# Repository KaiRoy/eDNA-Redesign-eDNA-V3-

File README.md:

# eDNA Board V3.0 - A Redesign of the OPEnS Lab's eDNA Control Board
A redesign of the Main Control Board for the eDNA Sampler

## Table of Contents

- [Description](#description)
- [Design](#design)
- [Current State](#current-state-of-the-project)
- [Post Project Notes](#post-project-notes)
- [Installation](#installation) <!-- Should I have Installation and Usage above or below the Design, Current State, Changes, etc? -->
- [Usage](#usage)
- [Credits](#credits)
- [License](#license)

## Description

I have worked on the eDNA project at the OPEnS Lab for the past two years and during that time I noticed a couple of things that I wanted to change about the current electronics board (Dubbed eDNA Electronics V2). Because of other responsiblities, I never had the time to make those changes so I decided to make a Project Course out of it to ensure that I would have the time. This meant I had to limit the number of changes that I wanted to make for time purposes. Here were the goals for the project/redesign:
- Allowing for 5V sensor support (mainly I2C sensor support)
- Redesigning the Power Management Circuits to allow for easier integration of wake-from-sleep interrupts
- Write Documentation for this version and the previous version, since no documentation does not exist

## Designs

Most of the circuits on this board have already been designed and I had no intention of fundamentally changing them in this redesign. The circuits that are being redesigned are the sleep/power management circuit and the logic level converter circuit. The other circuits only get changed on the PCB Layout level, changing as many two-terminal components from 1206 to 0805 and general rearrangement of the PCB Layout.

The power management (PM) system was designed to disable the output of the voltage regulator (Vreg). This would conserve a lot of power as most of the circuits and devices would be powered off, with only the RTC and parts of the PM circuit still functioning. This circuit work by using a D Flip Flop connected to the Microcontroller and the RTC to enable or disable the output of the Vreg Circuit. Because of this design, the microcontroller was completely off with only the RTC Interrupt able to wake up the microcontroller. This makes it difficult to add additional external interrupts to wake the system from sleep. We encountered this problem when we tried to add a button that would wake the system from sleep and trigger an operation.

Another project from the OPEnS Lab created a PM circuit that is used by the majority of projects at the OPEnS Lab, the eDNA project being one of the few projects that do not. This project, called the Hypnos Board, uses a series of MOSFETs to enable and disable power lines going to peripheral devices, leaving the microcontroller powered. We can further conserve power by putting the microctronller into a deep sleep. This will allow us to easily add new wake-from-sleep interrupts while still conserving power.

According to other employees at the OPEnS Lab and some online research the Adafruit Feather M0, the OPEnS Lab's Microcontroller of choice, consumes 1-2mA of current while in a software sleep. Based on the size of the battery, power consumption during operation, and the size of the battery, the approximate current draw while in sleep should be little enough that the sampler can complete a full 24 operations over the course of 30 days, which is what the eDNA Sampler was designed to be able to do. 

The change in the logic level converter circuit was needed because 5V I2C sensor support was desired for the eDNA Sampler. This is because many I2C sensors function off of 5V and limiting the system to only 3.3V I2C sensors can make it difficult to add desired features or functionality. The current logic level converter, a module from Sparkfun, only has 4-channels of conversion with three already in use. Since the circuit needed to be changed anyway, instead of using a module like the one from SparkFun, an IC was found to serve the purpose. The IC used in the v3.0 is the TXS0108E, an eight channel logic level converter.

## Current State of the Project

I was able to do some testing by the end of the term and discovered a couple of mistakes. These mistakes had to do with how I wired certain components up on at the schematic level. I misconnceted the Sleep LED and the RTC_INT Pull-Up Resistor. The sleep LED is less important but rewiring it to my always-on 3.3V line instead of my peripheral device 3.3V line allowed me to better see if the sleep switch/circuit was functioning correctly. The RTC_INT Pull-Up Resistor on the other had was a major error. I had connected the resistor to the Peripheral 3.3V line instead of the always-on 3.3V, meaning that the power would be cut during sleep. Since the RTC_INT is necessary for waking up, this caused a constant cycle of the sleep mode being enabled, the drop in voltage triggering the interrupt, the system waking up, realizing that it has not reached the desired wake-up time, and falling back asleep. 

These mistakes could have been caught if I spent more time at the planning and schematic levels review the design before moving onto the PCB design. Something I plan to allocate time for in future projects. Because of this wiring issues, this version of the board remains untested. There are plans to cut the necessary traces and solder splice wires to reconenct the components and continue testing.

## Post Project Notes

In the future I would spend a lot more time verifying the schematic level of my design to ensure that I have no obvious mistakes, such as the wiring mistakes that I made in the first version of this board. If I am working on a project that is time limited, I would be sure to allocate more than enough time to spend verifying my design/schematic before moving onto the development of the PCB. 

I would also use KiCad over EAGLE in the future if possible. Having used both of the EDA softwares, I have developed a preference towards KiCad over EAGLE due to KiCad's Hotkey and Shortcut based control scheme. This has made my workflows in KiCad feel much smoother to me than my workflows in EAGLE have. In addition, I have been using the free version of EAGLE which has limitations on what can be done in the software, while KiCad does not. 

Below are a list of changes that I would recommend be made in future version of this board. I have split it into two categories as there is a difference between the changes that I would personally like to make, and the changes that I would recommend to the OPEnS Lab. Since the OPEnS Lab cannot simply make changes for the sack of making changes, the changes I recommend are ones that I see having a better Benefit-Cost Ratio conisdering the current state of the Project. 

What I would recommend for the next OPEnS Lab Version:
- Find a new Voltage Regulator IC/Redesign the Vreg Circuit
	- This IC was chosen as it had an Enable pin and its was automotive grade. Since neither of these specifications are that important I would recommend looking into a new IC that is easier to come by, since this one has been very hard to purchase in the past. 
- Redesign the Shift Registers to use the existing SPI Pins on the Feather M0
	- If that is not possible with the current Shift Registers for any reason, I would recommend finiding new Shift Registers to use in the design.

For my own personal version (outside of the OPEnS Lab):
- Switch to an ESP32 based design
	- Deep Sleep Functionality
  	- Built in RTC and WiFi Modules
  	- Similar amount of I/O Pins
	- Larger Program Memory (Our debug code is limited by the size of the Feather M0 Program Memory)
- Redesign the PCB with the intention of purchasing them preassembled. 
	- This would allow for smaller componenets to be used, components too small to be easily assembled by hand. 
	- This would allow for a two-sided PCB design i.e components on either side of the PCB, something that is hard to do by hand.

## Installation

What EDA libraries and files are needed for this project?
- eDNA Library
- Various Component Libraries
<!-- Make a singular Library for all of the components Symbols and footprints -->
<!-- Insert a link to a library guide or make my own -->

<!-- Add a link to the firmware installation guide -->
<!-- Note which code version to use -->

<!--
## Usage

Provide instructions and examples for use. Include screenshots as needed.

To add a screenshot, create an `assets/images` folder in your repository and upload your screenshot to it. Then, using the relative filepath, add it to your README using the following syntax:

    ```md
    
    ```

## Features

If your project has a lot of features, list them here.

## Tests

-->

## Credits

List your collaborators, if any, with links to their GitHub profiles.
- Nathan Jesudason: Modifying the [Sampler Code](https://github.com/OPEnSLab-OSU/ednaServer/tree/54-revamp-sleep-system) Changes for testing

If you used any third-party assets that require attribution, list the creators with links to their primary web presence in this section.
- OPEnS Lab's [Hypnos Board V3.4](https://github.com/OPEnSLab-OSU/OPEnS-Hypnos)
- A branch of the [ednaServer](https://github.com/OPEnSLab-OSU/ednaServer/tree/54-revamp-sleep-system) code
<!-- Link the Symbols and Footprints used? -->

## License

Licensed under the [CERN-OHL-S-2.0](LICENSE.txt) License

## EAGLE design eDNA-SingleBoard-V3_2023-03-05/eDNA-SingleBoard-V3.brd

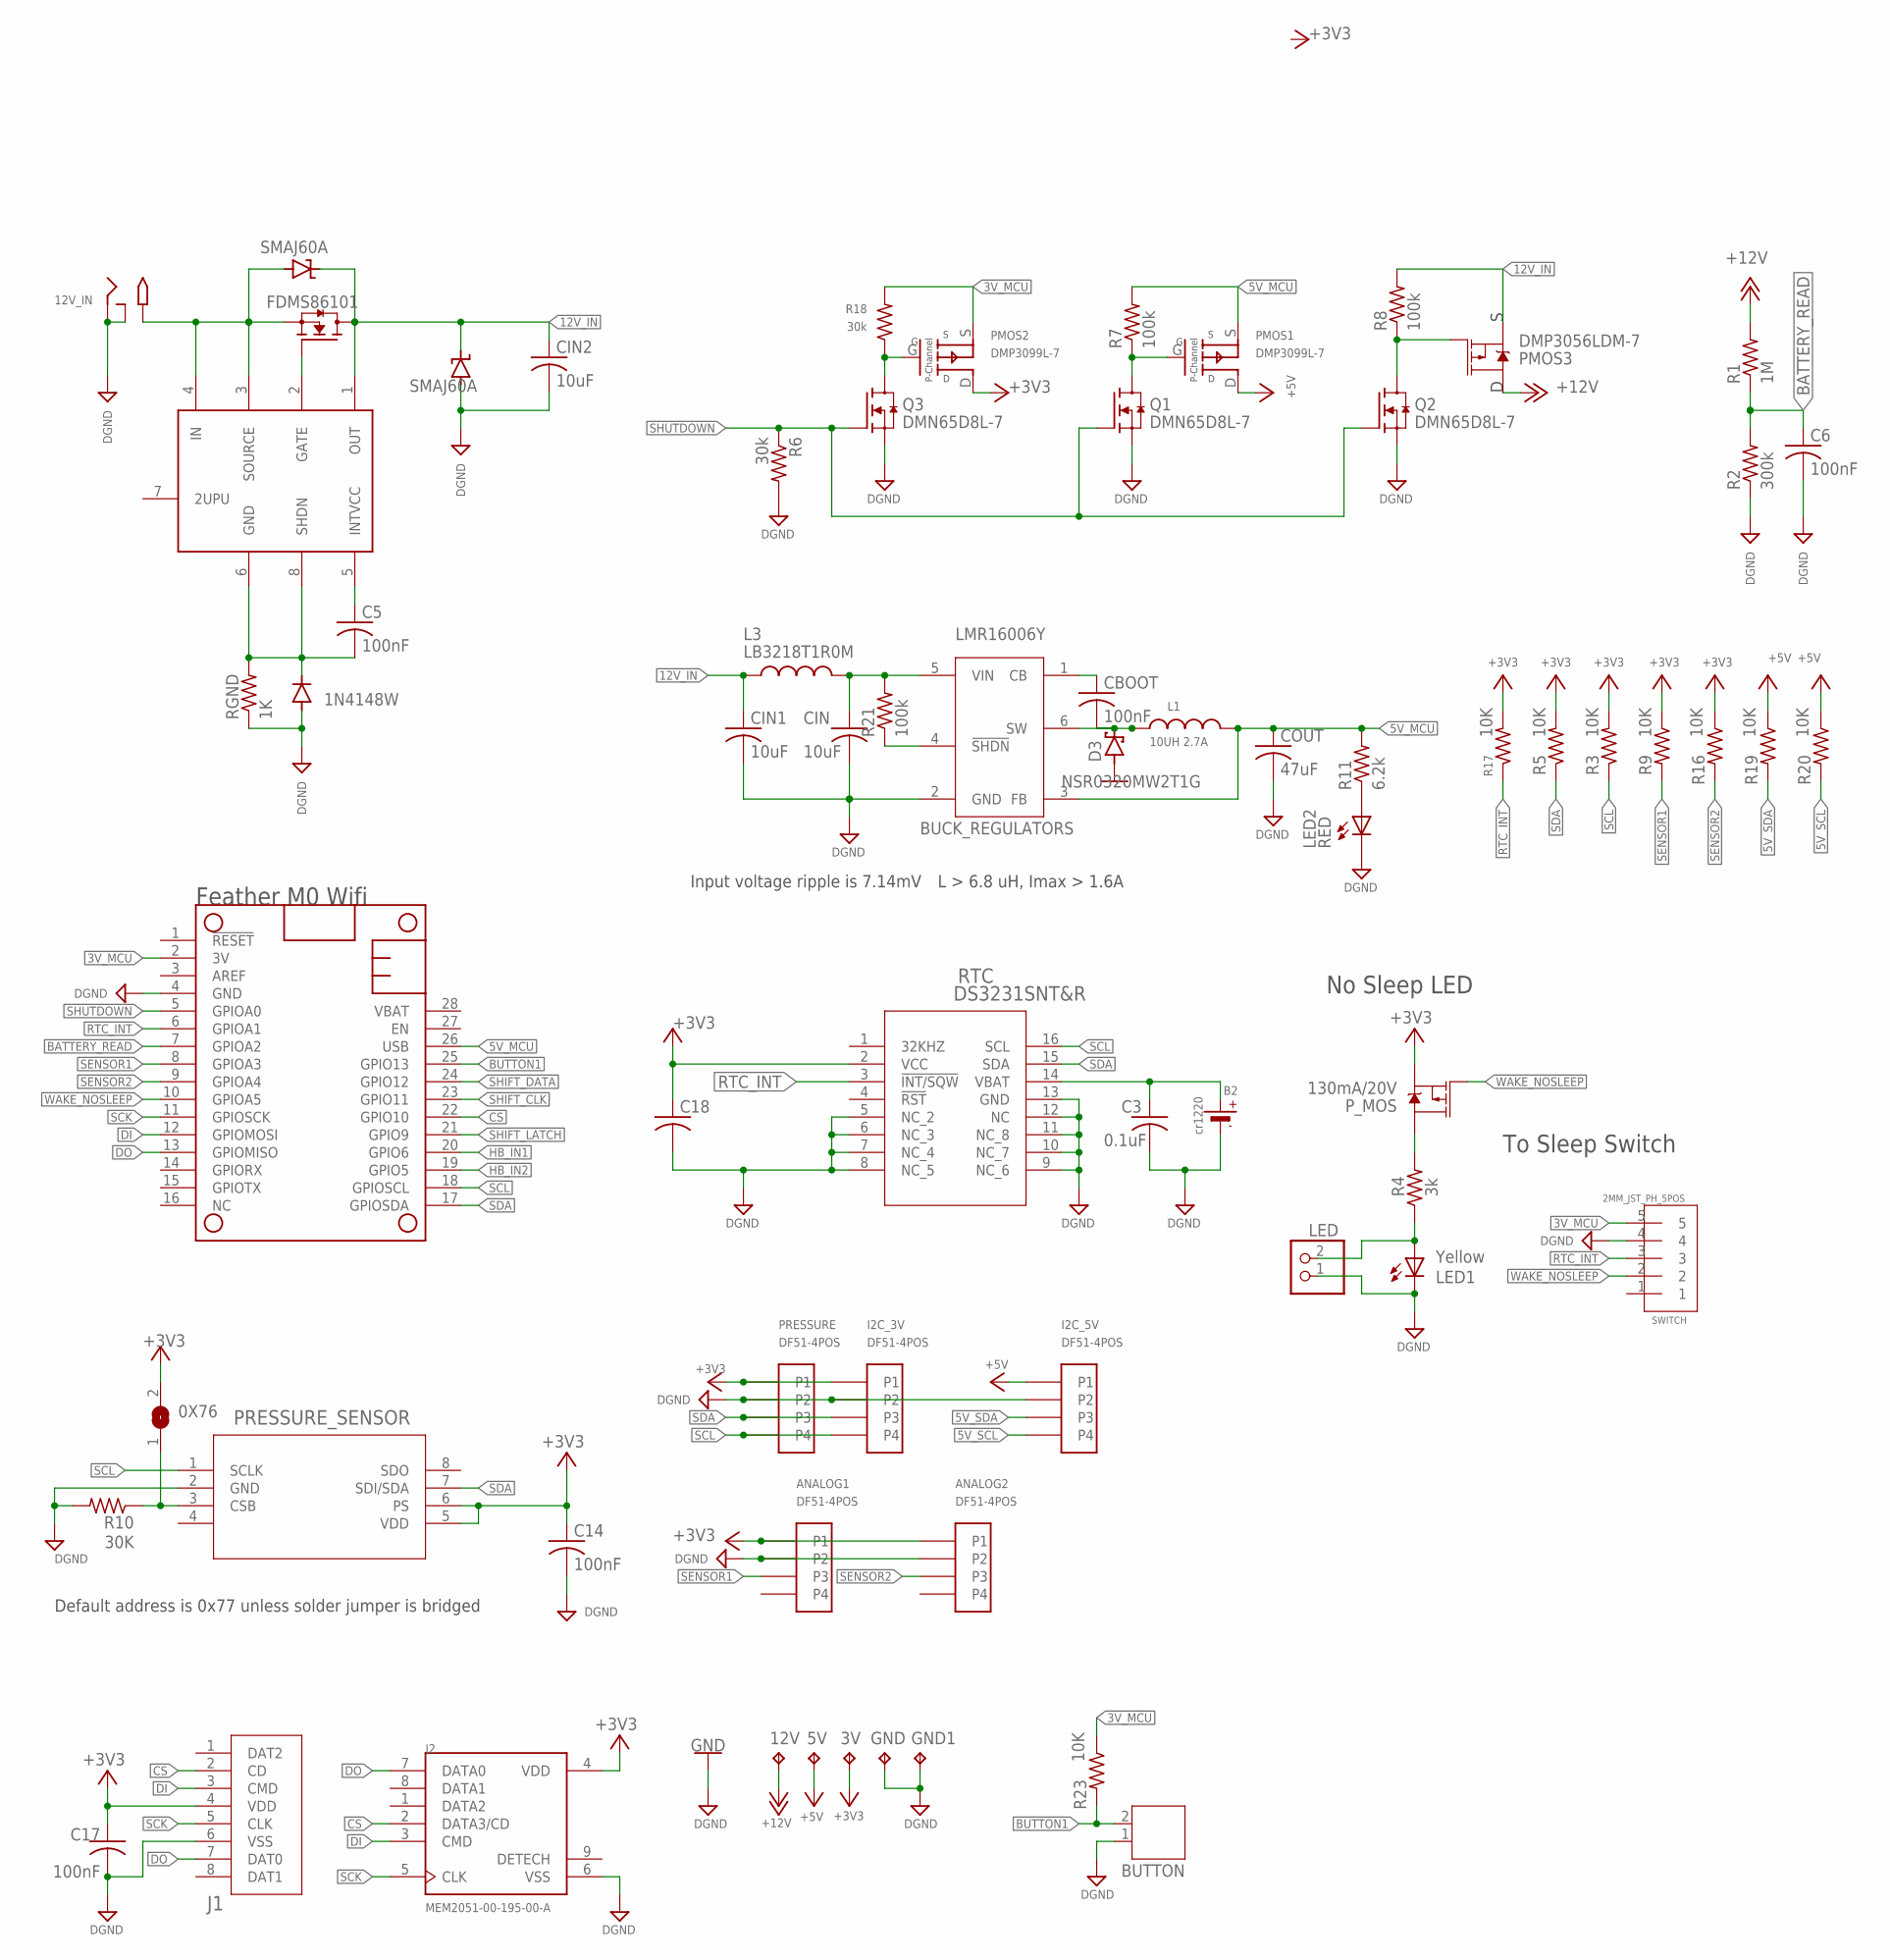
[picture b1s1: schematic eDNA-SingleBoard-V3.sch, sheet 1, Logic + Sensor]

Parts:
0X76: SJ
3V, 5V, 12V: TPPAD1-13; P1-13
12V_IN: 2.1MMJACKSMT; DCJACK_2MM_SMT
ANALOG1, ANALOG2: DF51-4POS
B2: cr1220; CR1220-2
BUTTON: JST-PH2
C3: 0.1uF; C0805
C5, C6, C14, C17, C18: 100nF; C0805
CBOOT: 100nF; C0805
CIN, CIN1, CIN2: 10uF; C0805
COUT: 47uF; C0805
D2: 1N4148W; SOD-123_MINI-SMA
D3: NSR0320MW2T1G; SOD323_ST
D4, D5: SMAJ60A; DO_214
GND, GND1: TPPAD1-13; P1-13
I2C_3V, I2C_5V: DF51-4POS
J1: PJS008U-3000-0; CONN_PJS008U-3000-0_YAM
J2: MEM2051-00-195-00-A; GCT_MEM2051-00-195-00-A
L1: 10UH 2.7A; WE-MAPI_40XX
L3: LB3218T1R0M; INDC3218X200N
LED: 2.5MM_JST_UP_2POS; JST_2POS_2.5MM_UP
LED1: Yellow; CHIPLED_0805
LED2: RED; CHIPLED_0805
MS1: FEATHERWING
NMOS: FDMS86101; 8-POWERTDFN
PMOS1, PMOS2: DMP3099L-7; SOT-23-3
PMOS3: DMP3056LDM-7; SOT23-6
PRESSURE: DF51-4POS
PRESSURE_SENSOR: MS580302BA01-00; MS5803-02BA01
P_MOS: 130mA/20V; SOT23-3
Q1, Q2, Q3: DMN65D8L-7; SOT23-S
R1: 1M; R0805
R2: 300k; R0805
R3, R5, R9, R16, R17, R19, R20, R23: 10K; R0805
R4: 3k; R0805
R6, R18: 30k; RES_1206
R7, R8, R21: 100k; RES_1206
R10: 30K; R0805
R11: 6.2k; R0805
RGND: 1K; R0805
RTC: DS3231SNT&R; 21-0042B_16
SWITCH: 2MM_JST_PH_5POS; 2MM_5POS_HEADER
U$7: LTC4372; SOP65P640X120-8N
VREG: BUCK_REGULATORS; SOT23-6@1

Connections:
3V_MCU: MS1.2 (3V), PMOS2.S, R18.2, R23.1, SWITCH.5
5V_MCU: COUT.1, L1.2, MS1.26 (USB), PMOS1.S, R7.2, R11.2, VREG.3 (FB)
5V_SCL: I2C_5V.P$4 (P4), R20.2; also elsewhere on the board
5V_SDA: I2C_5V.P$3 (P3), R19.2; also elsewhere on the board
12V_IN: CIN1.1, CIN2.1, D4.C, D5.C, L3.1, NMOS.5 (D), NMOS.6 (D), NMOS.7 (D), NMOS.8 (D), NMOS.9 (D), PMOS3.4 (S), R8.2, U$7.1 (OUT)
+3V3: 0X76.2, 3V.TP, ANALOG1.P$1 (P1), ANALOG2.P$1 (P1), C14.1, C17.1, C18.1, I2C_3V.P$1 (P1), J1.4 (VDD), J2.4 (VDD), PMOS2.D, PRESSURE.P$1 (P1), PRESSURE_SENSOR.5 (VDD), PRESSURE_SENSOR.6 (PS), P_MOS.2 (S), R3.2, R5.2, R9.1, R16.1, R17.2, RTC.2 (VCC); also elsewhere on the board
+5V: 5V.TP, I2C_5V.P$1 (P1), PMOS1.D, R19.1, R20.1; also elsewhere on the board
+12V: 12V.TP, PMOS3.1 (D), PMOS3.2 (D), PMOS3.5 (D), PMOS3.6 (D), R1.2; also elsewhere on the board
+12V_NON_PROTECT: 12V_IN.PWR2 (TIP), D5.A, NMOS.1 (S), NMOS.2 (S), NMOS.3 (S), U$7.3 (SOURCE), U$7.4 (IN)
BATTERY_READ: C6.1, MS1.7 (GPIOA2), R1.1, R2.2
BUTTON1: BUTTON.2, MS1.25 (GPIO13), R23.2
CS: J1.2 (CD), J2.2 (DATA3/CD), MS1.22 (GPIO10)
DGND: 12V_IN.GND (RING), 12V_IN.GNDBREAK (RING_SW), ANALOG1.P$2 (P2), ANALOG2.P$2 (P2), B2.-, BUTTON.1, C3.2, C6.2, C14.2, C17.2, C18.2, CIN.2, CIN1.2, CIN2.2, COUT.2, D2.A, D4.A, GND.TP, GND1.TP, I2C_3V.P$2 (P2), I2C_5V.P$2 (P2), J1.6 (VSS), J2.6 (VSS), LED.1, LED1.C, LED2.C, MS1.4 (GND), PRESSURE.P$2 (P2), PRESSURE_SENSOR.2 (GND), Q1.2 (S), Q2.2 (S), Q3.2 (S), R2.1, R6.2, R10.2, RGND.1, RTC.5 (NC_2), RTC.6 (NC_3), RTC.7 (NC_4), RTC.8 (NC_5), RTC.9 (NC_6), RTC.10 (NC_7), RTC.11 (NC_8), RTC.12 (NC), RTC.13 (GND), SWITCH.4, VREG.2 (GND); also elsewhere on the board
DI: J1.3 (CMD), J2.3 (CMD), MS1.12 (GPIOMOSI)
DO: J1.7 (DAT0), J2.7 (DATA0), MS1.13 (GPIOMISO)
GND: D3.A
HB_IN1: MS1.20 (GPIO6); also elsewhere on the board
HB_IN2: MS1.19 (GPIO5); also elsewhere on the board
unnamed: B2.+, C3.1, RTC.14 (VBAT)
unnamed: P_MOS.3 (D), R4.2
unnamed: PMOS3.3 (G), Q2.3 (D), R8.1
unnamed: 0X76.1, PRESSURE_SENSOR.3 (CSB), R10.1
unnamed: NMOS.4 (G), U$7.2 (GATE)
unnamed: LED.2, LED1.A, R4.1
unnamed: PMOS1.G, Q1.3 (D), R7.1
unnamed: LED2.A, R11.1
unnamed: R21.1, VREG.4 (!SHDN)
unnamed: PMOS2.G, Q3.3 (D), R18.1
unnamed: CIN.1, L3.2, R21.2, VREG.5 (VIN)
unnamed: CBOOT.1, VREG.1 (CB)
unnamed: CBOOT.2, D3.C, L1.1, VREG.6 (SW)
unnamed: C5.1, U$7.5 (INTVCC)
unnamed: C5.2, D2.C, RGND.2, U$7.6 (GND), U$7.8 (SHDN)
RTC_INT: MS1.6 (GPIOA1), R17.1, RTC.3 (!INT/SQW), SWITCH.3
SCK: J1.5 (CLK), J2.5 (CLK), MS1.11 (GPIOSCK)
SCL: I2C_3V.P$4 (P4), MS1.18 (GPIOSCL), PRESSURE.P$4 (P4), PRESSURE_SENSOR.1 (SCLK), R3.1, RTC.16 (SCL); also elsewhere on the board
SDA: I2C_3V.P$3 (P3), MS1.17 (GPIOSDA), PRESSURE.P$3 (P3), PRESSURE_SENSOR.7 (SDI/SDA), R5.1, RTC.15 (SDA); also elsewhere on the board
SENSOR1: ANALOG1.P$3 (P3), MS1.8 (GPIOA3), R9.2
SENSOR2: ANALOG2.P$3 (P3), MS1.9 (GPIOA4), R16.2
SHIFT_CLK: MS1.23 (GPIO11); also elsewhere on the board
SHIFT_DATA: MS1.24 (GPIO12); also elsewhere on the board
SHIFT_LATCH: MS1.21 (GPIO9); also elsewhere on the board
SHUTDOWN: MS1.5 (GPIOA0), Q1.1 (G), Q2.1 (G), Q3.1 (G), R6.1
WAKE_NOSLEEP: MS1.10 (GPIOA5), P_MOS.1 (G), SWITCH.2

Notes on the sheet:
No Sleep LED
Feather M0 Wifi
To Sleep Switch
Input voltage ripple is 7.14mV
L > 6.8 uH, Imax > 1.6A
Default address is 0x77 unless solder jumper is bridged

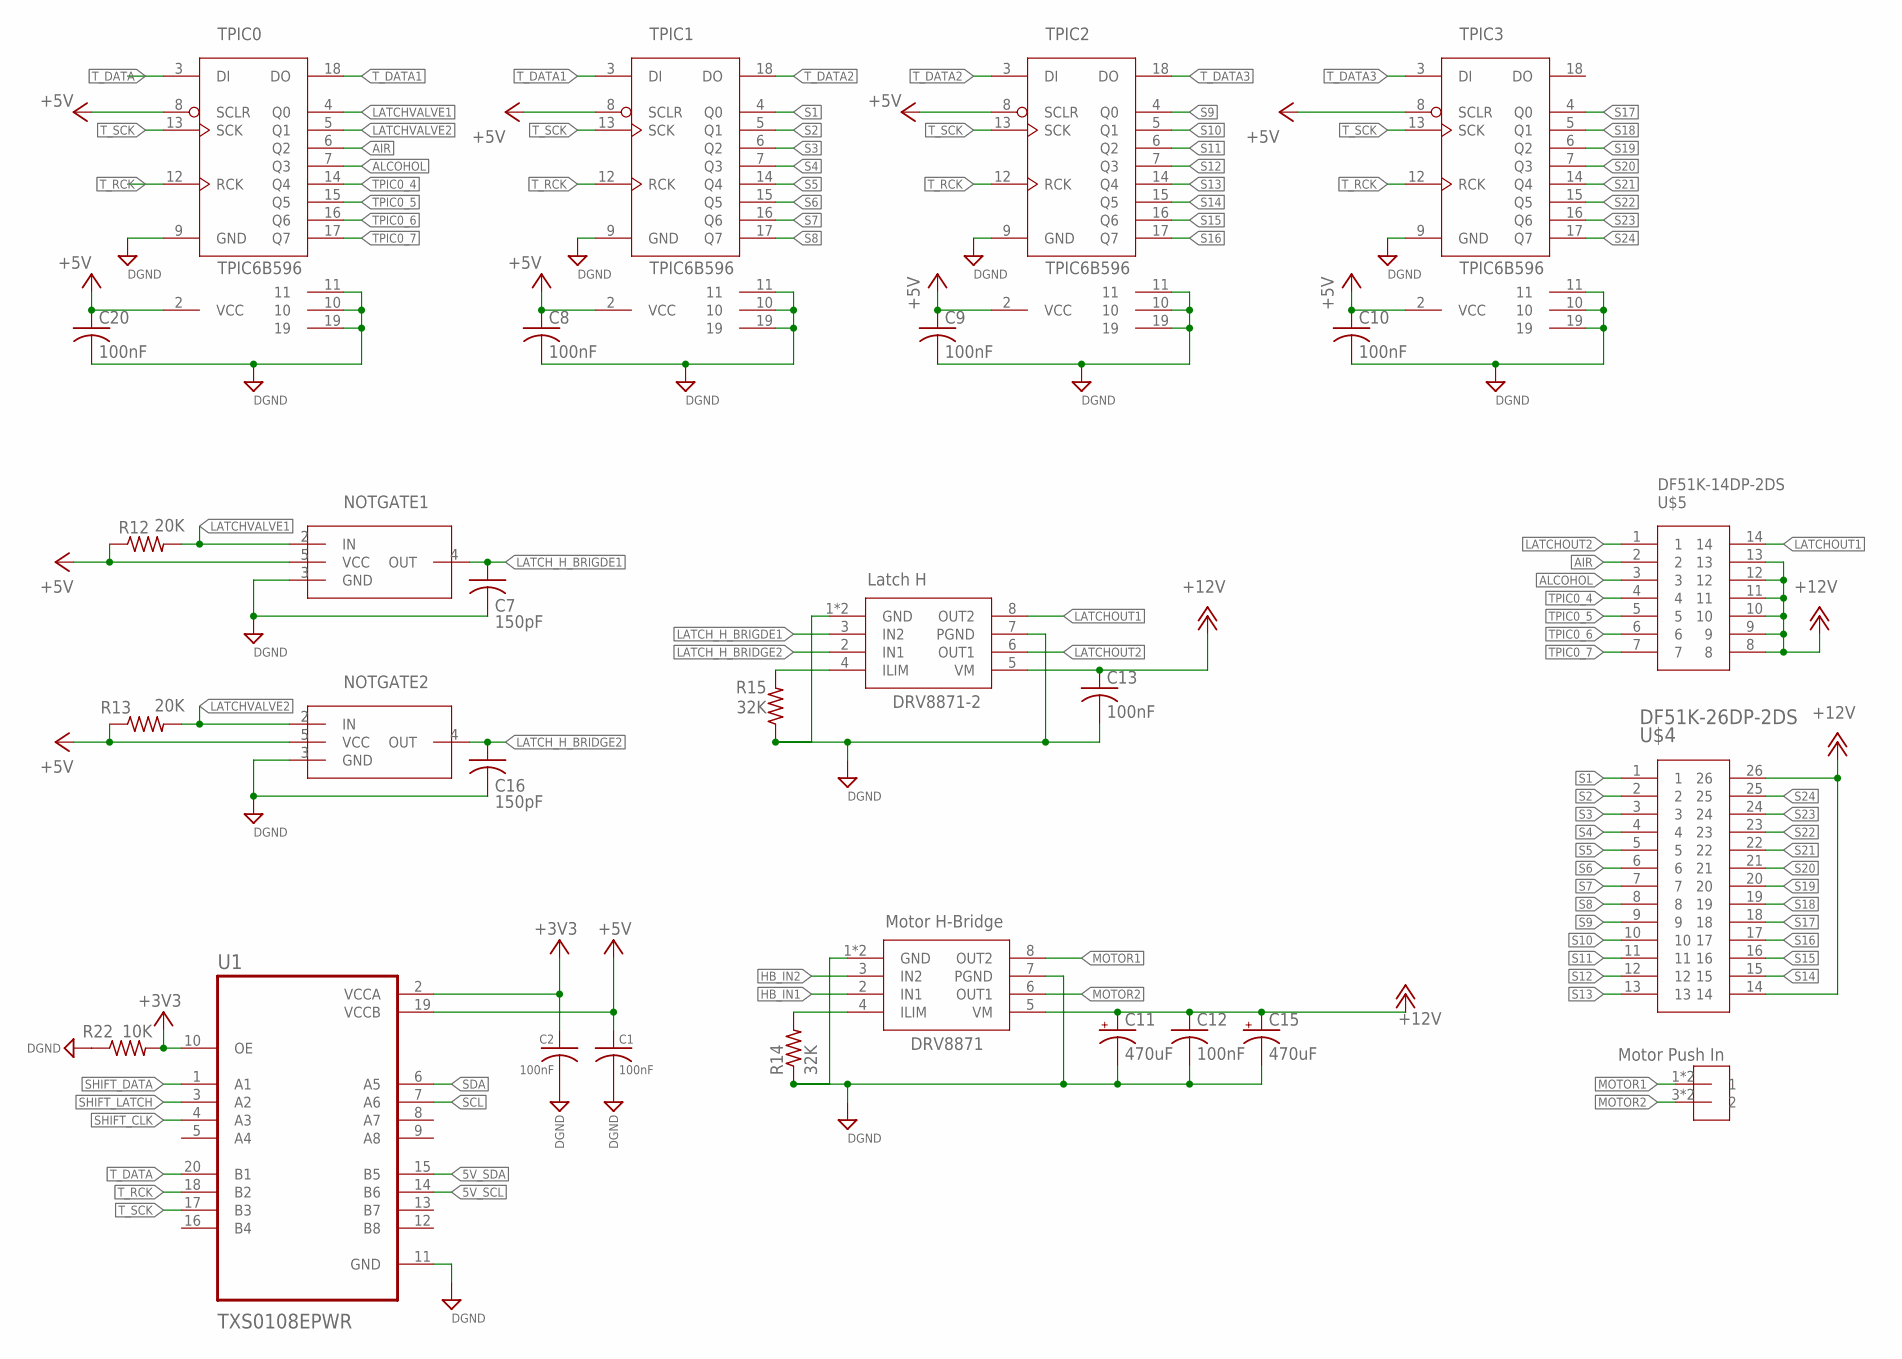
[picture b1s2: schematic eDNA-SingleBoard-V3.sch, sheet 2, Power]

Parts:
C1, C2, C8, C9, C10, C12, C13, C20: 100nF; C0805
C7, C16: 150pF; C0805
C11, C15: 470uF; 140CLH-0810
DRV8871: Motor H-Bridge; SOP8
DRV8871-2: Latch H; SOP8
NOTGATE1, NOTGATE2: NOT_GATE; SOT753
R12, R13: 20K; R0805
R14, R15: 32K; R0805
R22: 10K; R0805
TPIC0, TPIC1, TPIC2, TPIC3: TPIC6B596; DIP20
U1: TXS0108EPWR; SOP65P640X120-20N
U$2: Motor Push In; 3.5MM_DIP2
U$4: DF51K-26DP-2DS; DF51K-26DP-2DS-ANGLE
U$5: DF51K-14DP-2DS; DF51K-14DP-2DS-ANGLE

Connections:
5V_SCL: U1.14 (B6); also elsewhere on the board
5V_SDA: U1.15 (B5); also elsewhere on the board
+3V3: C2.1, R22.2, U1.2 (VCCA), U1.10 (OE); also elsewhere on the board
+5V: C1.1, C8.1, C9.1, C10.1, C20.1, NOTGATE1.5 (VCC), NOTGATE2.5 (VCC), R12.1, R13.1, TPIC0.2 (VCC), TPIC0.8 (SCLR), TPIC1.2 (VCC), TPIC1.8 (SCLR), TPIC2.2 (VCC), TPIC2.8 (SCLR), TPIC3.2 (VCC), TPIC3.8 (SCLR), U1.19 (VCCB); also elsewhere on the board
+12V: C11.+, C12.1, C13.1, C15.+, DRV8871.5 (VM), DRV8871-2.5 (VM), U$4.14, U$4.26, U$5.8, U$5.9, U$5.10, U$5.11, U$5.12, U$5.13; also elsewhere on the board
AIR: TPIC0.6 (Q2), U$5.2
ALCOHOL: TPIC0.7 (Q3), U$5.3
DGND: C1.2, C2.2, C7.2, C8.2, C9.2, C10.2, C11.-, C12.2, C13.2, C15.-, C16.2, C20.2, DRV8871.1 (GND), DRV8871.7 (PGND), DRV8871.GND, DRV8871-2.1 (GND), DRV8871-2.7 (PGND), DRV8871-2.GND, NOTGATE1.3 (GND), NOTGATE2.3 (GND), R14.1, R15.1, R22.1, TPIC0.9 (GND), TPIC0.10, TPIC0.11, TPIC0.19, TPIC1.9 (GND), TPIC1.10, TPIC1.11, TPIC1.19, TPIC2.9 (GND), TPIC2.10, TPIC2.11, TPIC2.19, TPIC3.9 (GND), TPIC3.10, TPIC3.11, TPIC3.19, U1.11 (GND); also elsewhere on the board
HB_IN1: DRV8871.2 (IN1); also elsewhere on the board
HB_IN2: DRV8871.3 (IN2); also elsewhere on the board
LATCHOUT1: DRV8871-2.8 (OUT2), U$5.14
LATCHOUT2: DRV8871-2.6 (OUT1), U$5.1
LATCHVALVE1: NOTGATE1.2 (IN), R12.2, TPIC0.4 (Q0)
LATCHVALVE2: NOTGATE2.2 (IN), R13.2, TPIC0.5 (Q1)
LATCH_H_BRIDGE2: C16.1, DRV8871-2.2 (IN1), NOTGATE2.4 (OUT)
LATCH_H_BRIGDE1: C7.1, DRV8871-2.3 (IN2), NOTGATE1.4 (OUT)
MOTOR1: DRV8871.8 (OUT2), U$2.1, U$2.2 (1)
MOTOR2: DRV8871.6 (OUT1), U$2.3 (2), U$2.4 (2)
unnamed: DRV8871.4 (ILIM), R14.2
unnamed: DRV8871-2.4 (ILIM), R15.2
S1: TPIC1.4 (Q0), U$4.1
S2: TPIC1.5 (Q1), U$4.2
S3: TPIC1.6 (Q2), U$4.3
S4: TPIC1.7 (Q3), U$4.4
S5: TPIC1.14 (Q4), U$4.5
S6: TPIC1.15 (Q5), U$4.6
S7: TPIC1.16 (Q6), U$4.7
S8: TPIC1.17 (Q7), U$4.8
S9: TPIC2.4 (Q0), U$4.9
S10: TPIC2.5 (Q1), U$4.10
S11: TPIC2.6 (Q2), U$4.11
S12: TPIC2.7 (Q3), U$4.12
S13: TPIC2.14 (Q4), U$4.13
S14: TPIC2.15 (Q5), U$4.15
S15: TPIC2.16 (Q6), U$4.16
S16: TPIC2.17 (Q7), U$4.17
S17: TPIC3.4 (Q0), U$4.18
S18: TPIC3.5 (Q1), U$4.19
S19: TPIC3.6 (Q2), U$4.20
S20: TPIC3.7 (Q3), U$4.21
S21: TPIC3.14 (Q4), U$4.22
S22: TPIC3.15 (Q5), U$4.23
S23: TPIC3.16 (Q6), U$4.24
S24: TPIC3.17 (Q7), U$4.25
SCL: U1.7 (A6); also elsewhere on the board
SDA: U1.6 (A5); also elsewhere on the board
SHIFT_CLK: U1.4 (A3); also elsewhere on the board
SHIFT_DATA: U1.1 (A1); also elsewhere on the board
SHIFT_LATCH: U1.3 (A2); also elsewhere on the board
TPIC0_4: TPIC0.14 (Q4), U$5.4
TPIC0_5: TPIC0.15 (Q5), U$5.5
TPIC0_6: TPIC0.16 (Q6), U$5.6
TPIC0_7: TPIC0.17 (Q7), U$5.7
T_DATA: TPIC0.3 (DI), U1.20 (B1)
T_DATA1: TPIC0.18 (DO), TPIC1.3 (DI)
T_DATA2: TPIC1.18 (DO), TPIC2.3 (DI)
T_DATA3: TPIC2.18 (DO), TPIC3.3 (DI)
T_RCK: TPIC0.12 (RCK), TPIC1.12 (RCK), TPIC2.12 (RCK), TPIC3.12 (RCK), U1.18 (B2)
T_SCK: TPIC0.13 (SCK), TPIC1.13 (SCK), TPIC2.13 (SCK), TPIC3.13 (SCK), U1.17 (B3)

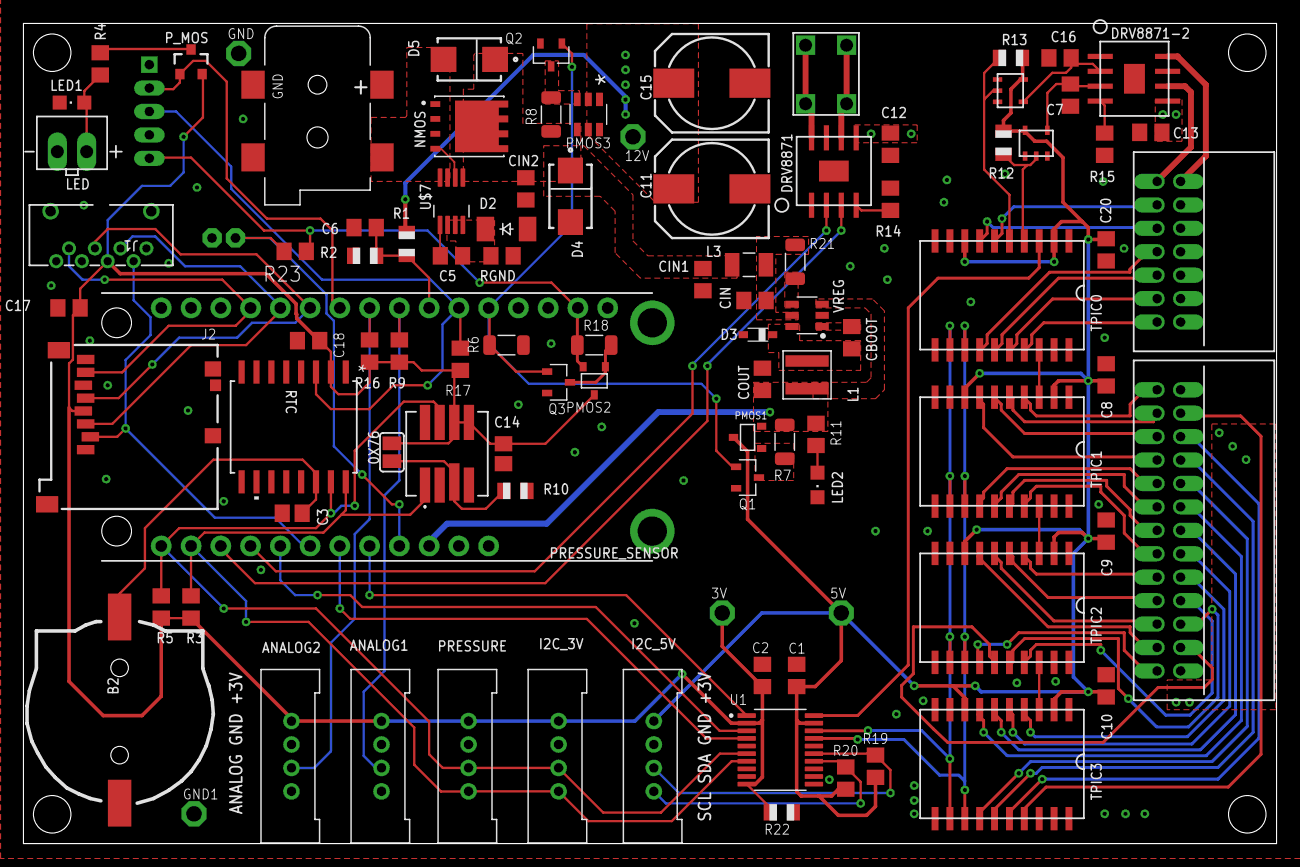
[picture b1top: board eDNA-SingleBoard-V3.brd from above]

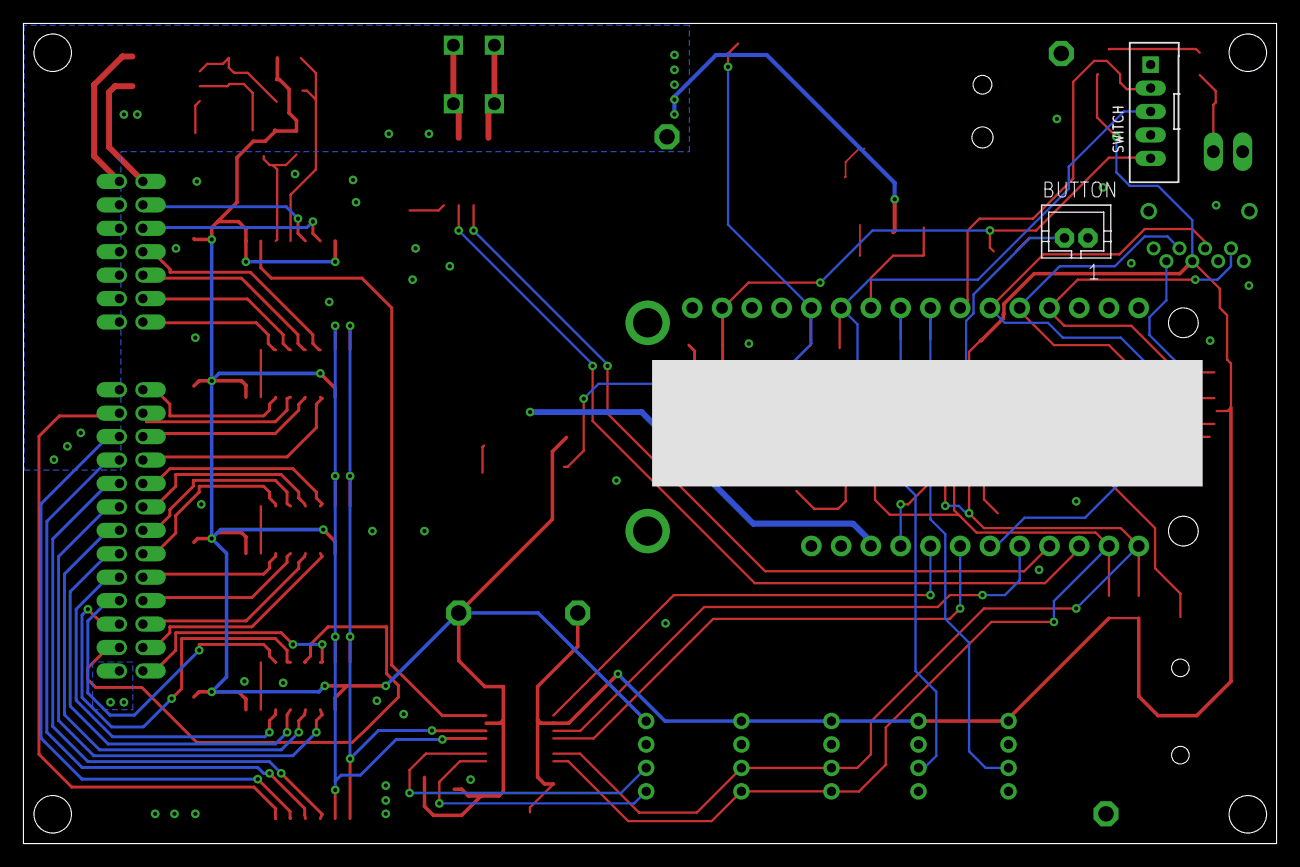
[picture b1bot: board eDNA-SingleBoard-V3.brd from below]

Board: 2 copper layers, 107.0 x 70.0 mm, 98 parts (2 on the bottom side), 89 nets.

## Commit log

2023-02-16 Added Existing Files
2023-02-26 Renamed the files
2023-02-27 Updated the SCH and PCB Files
    Nearly completed the update to the Schematic.
    Started to ripup all the traces on the PCB
2023-02-27 Updated Schematic
2023-03-01 Updated Schematic and PCB Files
2023-03-02 Updated SCH and PCB
2023-03-03 Update the PCB
2023-03-06 Added External Interrupt
2023-03-06 Added Silkscreen area for serial number
2023-03-11 Added Gerber Files
2023-04-09 Removed Unnecessary Backup Files
2023-05-04 Added images to README

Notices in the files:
parts and their libraries:
SparkFun-PowerSymbols: Licensing: Creative Commons ShareAlike 4.0 International - https://creativecommons.org/licenses/by-sa/4.0
microbuilder: This work is placed in the public domain, and may be freely used for commercial and non-commercial work with the following conditions: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
